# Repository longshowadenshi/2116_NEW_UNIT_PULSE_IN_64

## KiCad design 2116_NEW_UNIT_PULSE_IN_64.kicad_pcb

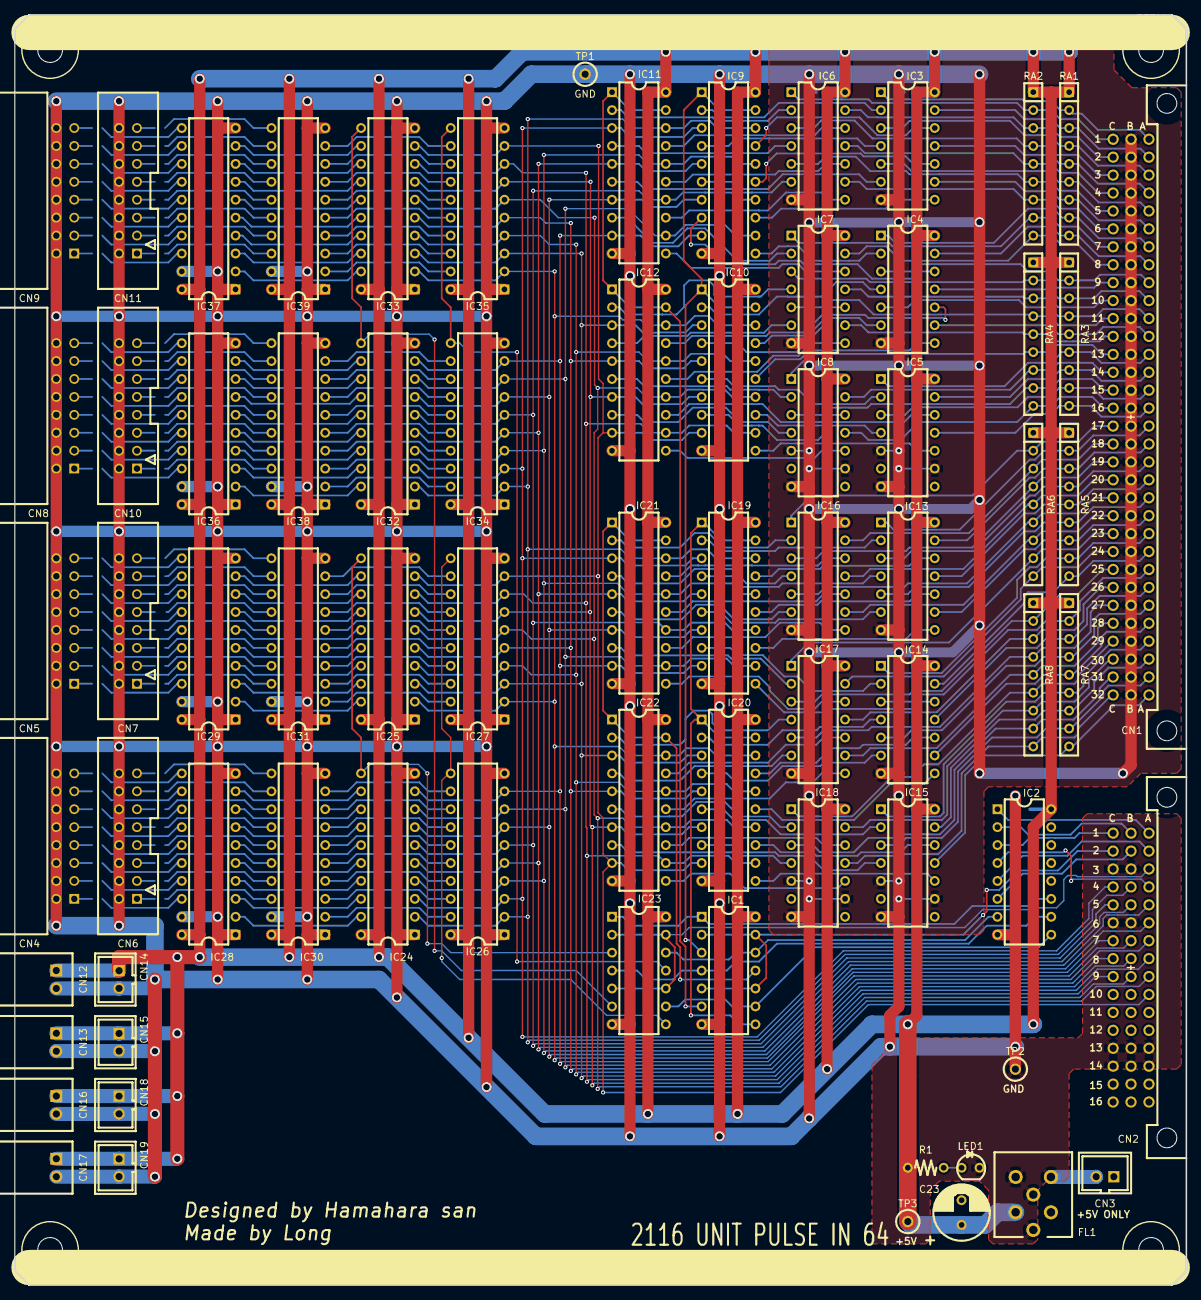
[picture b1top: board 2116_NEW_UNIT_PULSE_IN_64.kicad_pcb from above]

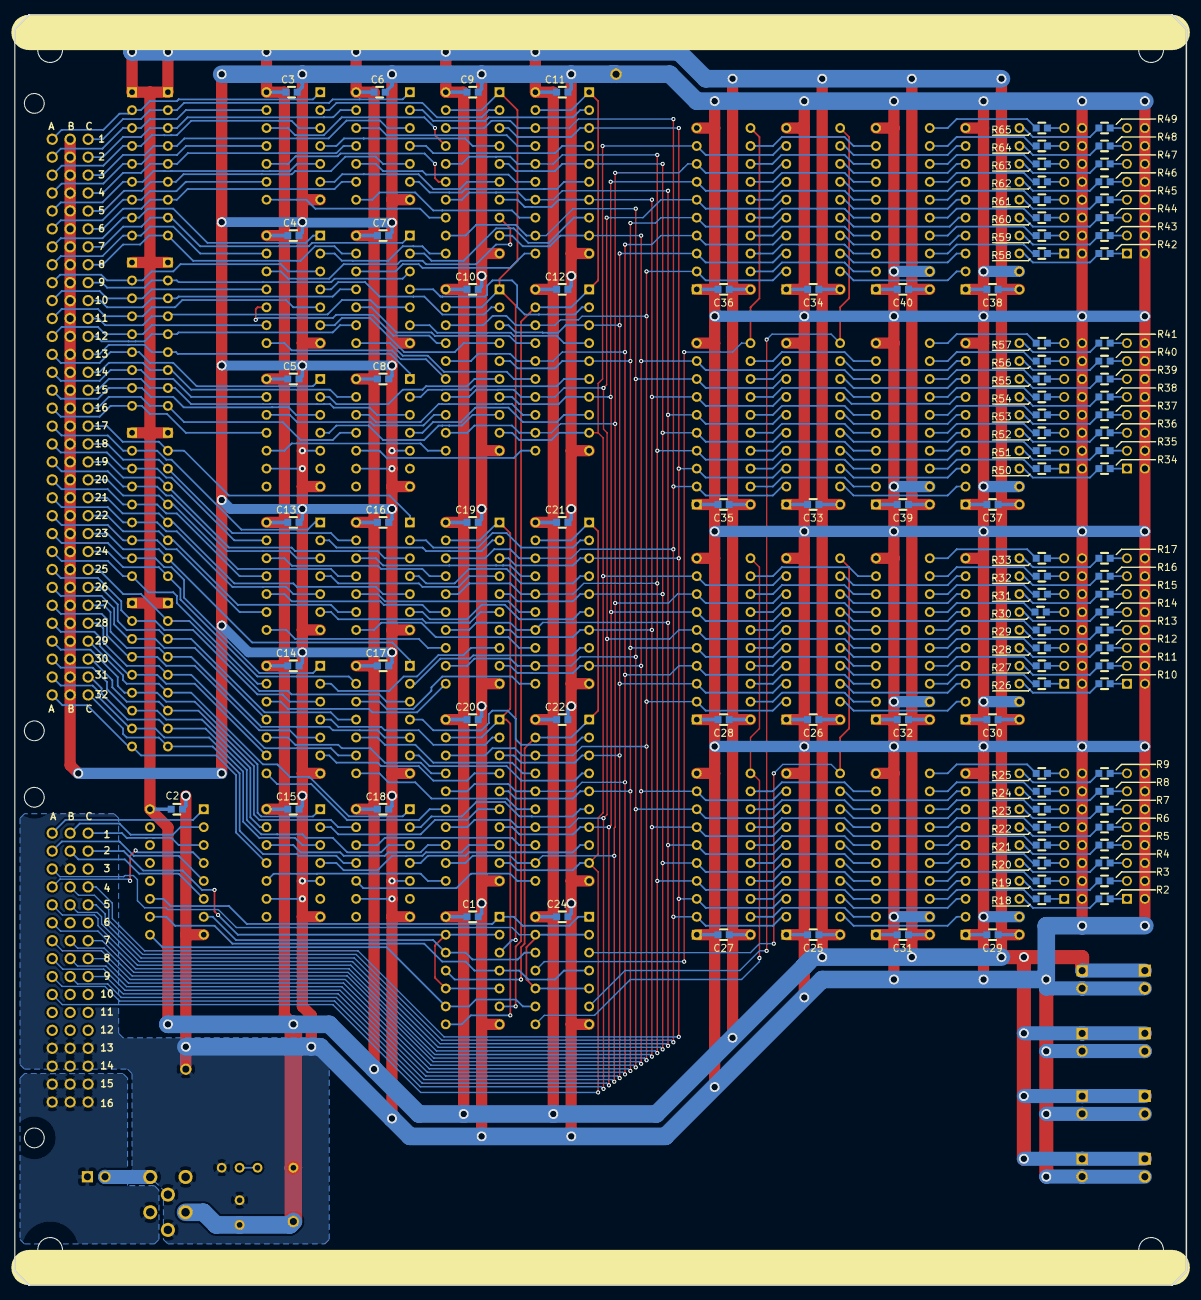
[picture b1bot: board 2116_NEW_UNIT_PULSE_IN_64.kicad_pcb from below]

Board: 2 copper layers, 166.0 x 180.0 mm, 176 parts (103 on the bottom side), 360 nets.

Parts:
C1, C2, C3, C4, C5, C6, C7, C8, C9, C10, C11, C12, C13, C14, C15, C16, C17, C18, C19, C20, C21, C22, C24, C25, C26, C27, C28, C29, C30, C31, C32, C33, C34, C35, C36, C37, C38, C39, C40: 0.1uF; C_0603
C23: 470uF/10V; CP_D8_P3R5
CN1: 09031966921; cn_09031966921
CN2: 09232486824; cn_09282486801
CN3, CN14, CN15, CN18, CN19: B2B-XH-A; cn_B2B-XH-A
CN4, CN5, CN8, CN9: HIF3FC-16PA-2.54DS; cn_HIF3FC-16PA-254DS
CN6, CN7, CN10, CN11: HIF3FC-16PA-2.54DSA; cn_HIF3FC-16PA-254DSA
CN12, CN13, CN16, CN17: S2B-XH-A
FL1: BNX002-01
IC1, IC23: 74HCT32; IC_DIP-14_W7.62mm
IC2: 74HCT138; ic_DIP-16_W7.62mm
IC3, IC4, IC5, IC6, IC7, IC8, IC13, IC14, IC15, IC16, IC17, IC18: 74HC14; IC_DIP-14_W7.62mm
IC9, IC10, IC11, IC12, IC19, IC20, IC21, IC22: 74HC244; ic_DIP-20_W7.62mm
IC24, IC25, IC26, IC27, IC32, IC33, IC34, IC35: 74HCT574; ic_DIP-20_W7.62mm
IC28, IC29, IC30, IC31, IC36, IC37, IC38, IC39: 74HCT541; ic_DIP-20_W7.62mm
LED1: GREEN; LED_D3.0mm_center
R1: 470; R_TH_5R08
R2, R3, R4, R5, R6, R7, R8, R9, R10, R11, R12, R13, R14, R15, R16, R17, R18, R19, R20, R21, R22, R23, R24, R25, R26, R27, R28, R29, R30, R31, R32, R33, R34, R35, R36, R37, R38, R39, R40, R41, R42, R43, R44, R45, R46, R47, R48, R49, R50, R51, R52, R53, R54, R55, R56, R57, R58, R59, R60, R61, R62, R63, R64, R65: 470; C_0603
RA1, RA2, RA3, RA4, RA5, RA6, RA7, RA8: 4.7K * 8; RKC1_8B8
TP1, TP2: ST-2-1; LC-2-G
TP3: LC-2-G

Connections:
+5V: C1.1, C2.1, C3.1, C4.1, C5.1, C6.1, C7.1, C8.1, C9.1, C10.1, C11.1, C12.1, C13.1, C14.1, C15.1, C16.1, C17.1, C18.1, C19.1, C20.1, C21.1, C22.1, C23.1, C24.1, C25.1, C26.1, C27.1, C28.1, C29.1, C30.1, C31.1, C32.1, C33.1, C34.1, C35.1, C36.1, C37.1, C38.1, C39.1, C40.1, CN12.1, CN13.1, CN14.1, CN15.1, CN16.1, CN17.1, CN18.1, CN19.1, FL1.2, IC1.14, IC2.16, IC3.14, IC4.14, IC5.14, IC6.14, IC7.14, IC8.14, IC9.20, IC10.20, IC11.20, IC12.20, IC13.14, IC14.14, IC15.14, IC16.14, IC17.14, IC18.14, IC19.20, IC20.20, IC21.20, IC22.20, IC23.14, IC24.20, IC25.20, IC26.20, IC27.20, IC28.20, IC29.20, IC30.20, IC31.20, IC32.20, IC33.20, IC34.20, IC35.20, IC36.20, IC37.20, IC38.20, IC39.20, R1.1, RA1.1, RA2.1, RA3.1, RA4.1, RA5.1, RA6.1, RA7.1, RA8.1, TP3.1
/A0: CN2.1A, IC2.1
/A1: CN2.1B, IC2.2
/A2: CN2.1C, IC2.3
/A3: CN2.2A, IC2.5
/A4: CN2.2B, IC2.6
/C_ENB: CN2.4A, IC2.4
/D0: CN2.4B, IC9.18, IC11.18, IC19.18, IC21.18, IC24.2, IC26.2, IC32.2, IC34.2
/D1: CN2.4C, IC9.3, IC11.3, IC19.3, IC21.3, IC24.3, IC26.3, IC32.3, IC34.3
/D2: CN2.5A, IC9.16, IC11.16, IC19.16, IC21.16, IC24.4, IC26.4, IC32.4, IC34.4
/D3: CN2.5B, IC9.5, IC11.5, IC19.5, IC21.5, IC24.5, IC26.5, IC32.5, IC34.5
/D4: CN2.5C, IC9.14, IC11.14, IC19.14, IC21.14, IC24.6, IC26.6, IC32.6, IC34.6
/D5: CN2.6A, IC9.7, IC11.7, IC19.7, IC21.7, IC24.7, IC26.7, IC32.7, IC34.7
/D6: CN2.7A, IC9.12, IC11.12, IC19.12, IC21.12, IC24.8, IC26.8, IC32.8, IC34.8
/D7: CN2.7B, IC9.9, IC11.9, IC19.9, IC21.9, IC24.9, IC26.9, IC32.9, IC34.9
/D8: CN2.7C, IC10.18, IC12.18, IC20.18, IC22.18, IC25.2, IC27.2, IC33.2, IC35.2
/D9: CN2.8A, IC10.3, IC12.3, IC20.3, IC22.3, IC25.3, IC27.3, IC33.3, IC35.3
/D10: CN2.8B, IC10.16, IC12.16, IC20.16, IC22.16, IC25.4, IC27.4, IC33.4, IC35.4
/D11: CN2.8C, IC10.5, IC12.5, IC20.5, IC22.5, IC25.5, IC27.5, IC33.5, IC35.5
/D12: CN2.9A, IC10.14, IC12.14, IC20.14, IC22.14, IC25.6, IC27.6, IC33.6, IC35.6
/D13: CN2.9B, IC10.7, IC12.7, IC20.7, IC22.7, IC25.7, IC27.7, IC33.7, IC35.7
/D14: CN2.9C, IC10.12, IC12.12, IC20.12, IC22.12, IC25.8, IC27.8, IC33.8, IC35.8
/D15: CN2.10A, IC10.9, IC12.9, IC20.9, IC22.9, IC25.9, IC27.9, IC33.9, IC35.9
/PULSE_IN_01/P01: CN1.1A, IC3.1, RA1.2
/PULSE_IN_01/P02: CN1.2A, IC3.13, RA1.3
/PULSE_IN_01/P03: CN1.3A, IC3.3, RA1.4
/PULSE_IN_01/P04: CN1.4A, IC3.11, RA1.5
/PULSE_IN_01/P05: CN1.5A, IC3.5, RA1.6
/PULSE_IN_01/P06: CN1.6A, IC3.9, RA1.7
/PULSE_IN_01/P07: CN1.7A, IC4.1, RA1.8
/PULSE_IN_01/P08: CN1.8A, IC4.13, RA1.9
/PULSE_IN_01/P09: CN1.9A, IC4.3, RA3.2
/PULSE_IN_01/P10: CN1.10A, IC4.11, RA3.3
/PULSE_IN_01/P11: CN1.11A, IC4.5, RA3.4
/PULSE_IN_01/P12: CN1.12A, IC4.9, RA3.5
/PULSE_IN_01/P13: CN1.13A, IC5.1, RA3.6
/PULSE_IN_01/P14: CN1.14A, IC5.13, RA3.7
/PULSE_IN_01/P15: CN1.15A, IC5.3, RA3.8
/PULSE_IN_01/P16: CN1.16A, IC5.11, RA3.9
/PULSE_IN_01/P17: CN1.1C, IC6.1, RA2.2
/PULSE_IN_01/P18: CN1.2C, IC6.13, RA2.3
/PULSE_IN_01/P19: CN1.3C, IC6.3, RA2.4
/PULSE_IN_01/P20: CN1.4C, IC6.11, RA2.5
/PULSE_IN_01/P21: CN1.5C, IC6.5, RA2.6
/PULSE_IN_01/P22: CN1.6C, IC6.9, RA2.7
/PULSE_IN_01/P23: CN1.7C, IC7.1, RA2.8
/PULSE_IN_01/P24: CN1.8C, IC7.13, RA2.9
/PULSE_IN_01/P25: CN1.9C, IC7.3, RA4.2
/PULSE_IN_01/P26: CN1.10C, IC7.11, RA4.3
/PULSE_IN_01/P27: CN1.11C, IC7.5, RA4.4
/PULSE_IN_01/P28: CN1.12C, IC7.9, RA4.5
/PULSE_IN_01/P29: CN1.13C, IC8.1, RA4.6
/PULSE_IN_01/P30: CN1.14C, IC8.13, RA4.7
/PULSE_IN_01/P31: CN1.15C, IC8.3, RA4.8
/PULSE_IN_01/P32: CN1.16C, IC8.11, RA4.9
/PULSE_IN_01/Q01: IC3.2, IC9.2
/PULSE_IN_01/Q02: IC3.12, IC9.17
/PULSE_IN_01/Q03: IC3.4, IC9.4
/PULSE_IN_01/Q04: IC3.10, IC9.15
/PULSE_IN_01/Q05: IC3.6, IC9.6
/PULSE_IN_01/Q06: IC3.8, IC9.13
/PULSE_IN_01/Q07: IC4.2, IC9.11
/PULSE_IN_01/Q08: IC4.12, IC9.8
/PULSE_IN_01/Q09: IC4.4, IC10.2
/PULSE_IN_01/Q10: IC4.10, IC10.17
/PULSE_IN_01/Q11: IC4.6, IC10.4
/PULSE_IN_01/Q12: IC4.8, IC10.15
/PULSE_IN_01/Q13: IC5.2, IC10.6
/PULSE_IN_01/Q14: IC5.12, IC10.13
/PULSE_IN_01/Q15: IC5.4, IC10.8
/PULSE_IN_01/Q16: IC5.10, IC10.11
/PULSE_IN_01/Q17: IC6.2, IC11.2
/PULSE_IN_01/Q18: IC6.12, IC11.17
/PULSE_IN_01/Q19: IC6.4, IC11.4
/PULSE_IN_01/Q20: IC6.10, IC11.15
/PULSE_IN_01/Q21: IC6.6, IC11.6
/PULSE_IN_01/Q22: IC6.8, IC11.13
/PULSE_IN_01/Q23: IC7.2, IC11.8
/PULSE_IN_01/Q24: IC7.12, IC11.11
/PULSE_IN_01/Q25: IC7.4, IC12.2
/PULSE_IN_01/Q26: IC7.10, IC12.17
/PULSE_IN_01/Q27: IC7.6, IC12.4
/PULSE_IN_01/Q28: IC7.8, IC12.15
/PULSE_IN_01/Q29: IC8.2, IC12.6
/PULSE_IN_01/Q30: IC8.12, IC12.13
/PULSE_IN_01/Q31: IC8.4, IC12.8
/PULSE_IN_01/Q32: IC8.10, IC12.11
/PULSE_IN_02/P33: CN1.17A, IC13.1, RA5.2
/PULSE_IN_02/P34: CN1.18A, IC13.13, RA5.3
/PULSE_IN_02/P35: CN1.19A, IC13.3, RA5.4
/PULSE_IN_02/P36: CN1.20A, IC13.11, RA5.5
/PULSE_IN_02/P37: CN1.21A, IC13.5, RA5.6
/PULSE_IN_02/P38: CN1.22A, IC13.9, RA5.7
/PULSE_IN_02/P39: CN1.23A, IC14.1, RA5.8
/PULSE_IN_02/P40: CN1.24A, IC14.13, RA5.9
/PULSE_IN_02/P41: CN1.25A, IC14.3, RA7.2
/PULSE_IN_02/P42: CN1.26A, IC14.11, RA7.3
/PULSE_IN_02/P43: CN1.27A, IC14.5, RA7.4
/PULSE_IN_02/P44: CN1.28A, IC14.9, RA7.5
/PULSE_IN_02/P45: CN1.29A, IC15.1, RA7.6
/PULSE_IN_02/P46: CN1.30A, IC15.13, RA7.7
/PULSE_IN_02/P47: CN1.31A, IC15.3, RA7.8
/PULSE_IN_02/P48: CN1.32A, IC15.11, RA7.9
/PULSE_IN_02/P49: CN1.17C, IC16.1, RA6.2
/PULSE_IN_02/P50: CN1.18C, IC16.13, RA6.3
/PULSE_IN_02/P51: CN1.19C, IC16.3, RA6.4
/PULSE_IN_02/P52: CN1.20C, IC16.11, RA6.5
/PULSE_IN_02/P53: CN1.21C, IC16.5, RA6.6
/PULSE_IN_02/P54: CN1.22C, IC16.9, RA6.7
/PULSE_IN_02/P55: CN1.23C, IC17.1, RA6.8
/PULSE_IN_02/P56: CN1.24C, IC17.13, RA6.9
/PULSE_IN_02/P57: CN1.25C, IC17.3, RA8.2
/PULSE_IN_02/P58: CN1.26C, IC17.11, RA8.3
/PULSE_IN_02/P59: CN1.27C, IC17.5, RA8.4
/PULSE_IN_02/P60: CN1.28C, IC17.9, RA8.5
/PULSE_IN_02/P61: CN1.29C, IC18.1, RA8.6
/PULSE_IN_02/P62: CN1.30C, IC18.13, RA8.7
/PULSE_IN_02/P63: CN1.31C, IC18.3, RA8.8
/PULSE_IN_02/P64: CN1.32C, IC18.11, RA8.9
/PULSE_IN_02/Q33: IC13.2, IC19.2
/PULSE_IN_02/Q34: IC13.12, IC19.17
/PULSE_IN_02/Q35: IC13.4, IC19.4
/PULSE_IN_02/Q36: IC13.10, IC19.15
/PULSE_IN_02/Q37: IC13.6, IC19.6
/PULSE_IN_02/Q38: IC13.8, IC19.13
/PULSE_IN_02/Q39: IC14.2, IC19.8
/PULSE_IN_02/Q40: IC14.12, IC19.11
/PULSE_IN_02/Q41: IC14.4, IC20.2
/PULSE_IN_02/Q42: IC14.10, IC20.17
/PULSE_IN_02/Q43: IC14.6, IC20.4
/PULSE_IN_02/Q44: IC14.8, IC20.15
/PULSE_IN_02/Q45: IC15.2, IC20.6
/PULSE_IN_02/Q46: IC15.12, IC20.13
/PULSE_IN_02/Q47: IC15.4, IC20.8
/PULSE_IN_02/Q48: IC15.10, IC20.11
/PULSE_IN_02/Q49: IC16.2, IC21.2
/PULSE_IN_02/Q50: IC16.12, IC21.17
/PULSE_IN_02/Q51: IC16.4, IC21.4
/PULSE_IN_02/Q52: IC16.10, IC21.15
/PULSE_IN_02/Q53: IC16.6, IC21.6
/PULSE_IN_02/Q54: IC16.8, IC21.13
/PULSE_IN_02/Q55: IC17.2, IC21.8
/PULSE_IN_02/Q56: IC17.12, IC21.11
/PULSE_IN_02/Q57: IC17.4, IC22.2
/PULSE_IN_02/Q58: IC17.10, IC22.17
/PULSE_IN_02/Q59: IC17.6, IC22.4
/PULSE_IN_02/Q60: IC17.8, IC22.15
/PULSE_IN_02/Q61: IC18.2, IC22.6
/PULSE_IN_02/Q62: IC18.12, IC22.13
/PULSE_IN_02/Q63: IC18.4, IC22.8
/PULSE_IN_02/Q64: IC18.10, IC22.11
/PULSE_OUT_01/OUT01: IC28.18, R2.1
/PULSE_OUT_01/OUT02: IC28.17, R3.1
/PULSE_OUT_01/OUT03: IC28.16, R4.1
/PULSE_OUT_01/OUT04: IC28.15, R5.1
/PULSE_OUT_01/OUT05: IC28.14, R6.1
/PULSE_OUT_01/OUT06: IC28.13, R7.1
/PULSE_OUT_01/OUT07: IC28.12, R8.1
/PULSE_OUT_01/OUT08: IC28.11, R9.1
/PULSE_OUT_01/OUT09: IC29.18, R10.1
/PULSE_OUT_01/OUT10: IC29.17, R11.1
/PULSE_OUT_01/OUT11: IC29.16, R12.1
/PULSE_OUT_01/OUT12: IC29.15, R13.1
/PULSE_OUT_01/OUT13: IC29.14, R14.1
/PULSE_OUT_01/OUT14: IC29.13, R15.1
/PULSE_OUT_01/OUT15: IC29.12, R16.1
/PULSE_OUT_01/OUT16: IC29.11, R17.1
/PULSE_OUT_01/OUT33: IC30.18, R18.1
/PULSE_OUT_01/OUT34: IC30.17, R19.1
/PULSE_OUT_01/OUT35: IC30.16, R20.1
/PULSE_OUT_01/OUT36: IC30.15, R21.1
/PULSE_OUT_01/OUT37: IC30.14, R22.1
/PULSE_OUT_01/OUT38: IC30.13, R23.1
/PULSE_OUT_01/OUT39: IC30.12, R24.1
/PULSE_OUT_01/OUT40: IC30.11, R25.1
/PULSE_OUT_01/OUT41: IC31.18, R26.1
/PULSE_OUT_01/OUT42: IC31.17, R27.1
/PULSE_OUT_01/OUT43: IC31.16, R28.1
/PULSE_OUT_01/OUT44: IC31.15, R29.1
/PULSE_OUT_01/OUT45: IC31.14, R30.1
/PULSE_OUT_01/OUT46: IC31.13, R31.1
/PULSE_OUT_01/OUT47: IC31.12, R32.1
/PULSE_OUT_01/OUT48: IC31.11, R33.1
/PULSE_OUT_01/Q01: IC24.19, IC28.2
/PULSE_OUT_01/Q02: IC24.18, IC28.3
/PULSE_OUT_01/Q03: IC24.17, IC28.4
/PULSE_OUT_01/Q04: IC24.16, IC28.5
/PULSE_OUT_01/Q05: IC24.15, IC28.6
/PULSE_OUT_01/Q06: IC24.14, IC28.7
/PULSE_OUT_01/Q07: IC24.13, IC28.8
/PULSE_OUT_01/Q08: IC24.12, IC28.9
/PULSE_OUT_01/Q09: IC25.19, IC29.2
/PULSE_OUT_01/Q10: IC25.18, IC29.3
/PULSE_OUT_01/Q11: IC25.17, IC29.4
/PULSE_OUT_01/Q12: IC25.16, IC29.5
/PULSE_OUT_01/Q13: IC25.15, IC29.6
/PULSE_OUT_01/Q14: IC25.14, IC29.7
/PULSE_OUT_01/Q15: IC25.13, IC29.8
/PULSE_OUT_01/Q16: IC25.12, IC29.9
/PULSE_OUT_01/Q33: IC26.19, IC30.2
/PULSE_OUT_01/Q34: IC26.18, IC30.3
/PULSE_OUT_01/Q35: IC26.17, IC30.4
/PULSE_OUT_01/Q36: IC26.16, IC30.5
/PULSE_OUT_01/Q37: IC26.15, IC30.6
/PULSE_OUT_01/Q38: IC26.14, IC30.7
/PULSE_OUT_01/Q39: IC26.13, IC30.8
/PULSE_OUT_01/Q40: IC26.12, IC30.9
/PULSE_OUT_01/Q41: IC27.19, IC31.2
/PULSE_OUT_01/Q42: IC27.18, IC31.3
/PULSE_OUT_01/Q43: IC27.17, IC31.4
/PULSE_OUT_01/Q44: IC27.16, IC31.5
/PULSE_OUT_01/Q45: IC27.15, IC31.6
/PULSE_OUT_01/Q46: IC27.14, IC31.7
/PULSE_OUT_01/Q47: IC27.13, IC31.8
/PULSE_OUT_01/Q48: IC27.12, IC31.9
/PULSE_OUT_02/OUT17: IC36.18, R34.1
/PULSE_OUT_02/OUT18: IC36.17, R35.1
/PULSE_OUT_02/OUT19: IC36.16, R36.1
/PULSE_OUT_02/OUT20: IC36.15, R37.1
/PULSE_OUT_02/OUT21: IC36.14, R38.1
/PULSE_OUT_02/OUT22: IC36.13, R39.1
/PULSE_OUT_02/OUT23: IC36.12, R40.1
/PULSE_OUT_02/OUT24: IC36.11, R41.1
/PULSE_OUT_02/OUT25: IC37.18, R42.1
/PULSE_OUT_02/OUT26: IC37.17, R43.1
/PULSE_OUT_02/OUT27: IC37.16, R44.1
/PULSE_OUT_02/OUT28: IC37.15, R45.1
/PULSE_OUT_02/OUT29: IC37.14, R46.1
/PULSE_OUT_02/OUT30: IC37.13, R47.1
/PULSE_OUT_02/OUT31: IC37.12, R48.1
/PULSE_OUT_02/OUT32: IC37.11, R49.1
/PULSE_OUT_02/OUT49: IC38.18, R50.1
/PULSE_OUT_02/OUT50: IC38.17, R51.1
/PULSE_OUT_02/OUT51: IC38.16, R52.1
/PULSE_OUT_02/OUT52: IC38.15, R53.1
/PULSE_OUT_02/OUT53: IC38.14, R54.1
/PULSE_OUT_02/OUT54: IC38.13, R55.1
/PULSE_OUT_02/OUT55: IC38.12, R56.1
/PULSE_OUT_02/OUT56: IC38.11, R57.1
/PULSE_OUT_02/OUT57: IC39.18, R58.1
/PULSE_OUT_02/OUT58: IC39.17, R59.1
/PULSE_OUT_02/OUT59: IC39.16, R60.1
/PULSE_OUT_02/OUT60: IC39.15, R61.1
/PULSE_OUT_02/OUT61: IC39.14, R62.1
/PULSE_OUT_02/OUT62: IC39.13, R63.1
/PULSE_OUT_02/OUT63: IC39.12, R64.1
/PULSE_OUT_02/OUT64: IC39.11, R65.1
/PULSE_OUT_02/Q17: IC32.19, IC36.2
/PULSE_OUT_02/Q18: IC32.18, IC36.3
/PULSE_OUT_02/Q19: IC32.17, IC36.4
/PULSE_OUT_02/Q20: IC32.16, IC36.5
/PULSE_OUT_02/Q21: IC32.15, IC36.6
/PULSE_OUT_02/Q22: IC32.14, IC36.7
/PULSE_OUT_02/Q23: IC32.13, IC36.8
/PULSE_OUT_02/Q24: IC32.12, IC36.9
/PULSE_OUT_02/Q25: IC33.19, IC37.2
/PULSE_OUT_02/Q26: IC33.18, IC37.3
/PULSE_OUT_02/Q27: IC33.17, IC37.4
/PULSE_OUT_02/Q28: IC33.16, IC37.5
/PULSE_OUT_02/Q29: IC33.15, IC37.6
/PULSE_OUT_02/Q30: IC33.14, IC37.7
/PULSE_OUT_02/Q31: IC33.13, IC37.8
/PULSE_OUT_02/Q32: IC33.12, IC37.9
/PULSE_OUT_02/Q49: IC34.19, IC38.2
/PULSE_OUT_02/Q50: IC34.18, IC38.3
/PULSE_OUT_02/Q51: IC34.17, IC38.4
/PULSE_OUT_02/Q52: IC34.16, IC38.5
/PULSE_OUT_02/Q53: IC34.15, IC38.6
/PULSE_OUT_02/Q54: IC34.14, IC38.7
/PULSE_OUT_02/Q55: IC34.13, IC38.8
/PULSE_OUT_02/Q56: IC34.12, IC38.9
/PULSE_OUT_02/Q57: IC35.19, IC39.2
/PULSE_OUT_02/Q58: IC35.18, IC39.3
/PULSE_OUT_02/Q59: IC35.17, IC39.4
/PULSE_OUT_02/Q60: IC35.16, IC39.5
/PULSE_OUT_02/Q61: IC35.15, IC39.6
/PULSE_OUT_02/Q62: IC35.14, IC39.7
/PULSE_OUT_02/Q63: IC35.13, IC39.8
/PULSE_OUT_02/Q64: IC35.12, IC39.9
/RD: CN2.2C, IC1.2, IC1.5, IC1.10, IC1.13
/SEL00: IC1.3, IC9.1, IC9.19, IC10.1, IC10.19
/SEL01: IC1.6, IC11.1, IC11.19, IC12.1, IC12.19
/SEL02: IC1.8, IC19.1, IC19.19, IC20.1, IC20.19
/SEL03: IC1.11, IC21.1, IC21.19, IC22.1, IC22.19
/W00: IC23.3, IC24.11, IC25.11
/W01: IC23.6, IC32.11, IC33.11
/W02: IC23.8, IC26.11, IC27.11
/W03: IC23.11, IC34.11, IC35.11
/WR: CN2.3A, IC23.2, IC23.5, IC23.10, IC23.13
GND: C1.2, C2.2, C3.2, C4.2, C5.2, C6.2, C7.2, C8.2, C9.2, C10.2, C11.2, C12.2, C13.2, C14.2, C15.2, C16.2, C17.2, C18.2, C19.2, C20.2, C21.2, C22.2, C23.2, C24.2, C25.2, C26.2, C27.2, C28.2, C29.2, C30.2, C31.2, C32.2, C33.2, C34.2, C35.2, C36.2, C37.2, C38.2, C39.2, C40.2, CN1.1B, CN1.2B, CN1.3B, CN1.4B, CN1.5B, CN1.6B, CN1.7B, CN1.8B, CN1.9B, CN1.10B, CN1.11B, CN1.12B, CN1.13B, CN1.14B, CN1.15B, CN1.16B, CN1.17B, CN1.18B, CN1.19B, CN1.20B, CN1.21B, CN1.22B, CN1.23B, CN1.24B, CN1.25B, CN1.26B, CN1.27B, CN1.28B, CN1.29B, CN1.30B, CN1.31B, CN1.32B, CN2.3B, CN2.3C, CN2.6B, CN2.6C, CN2.13A, CN2.13B, CN2.13C, CN2.14A, CN2.14B, CN2.14C, CN3.2, CN4.2, CN4.4, CN4.6, CN4.8, CN4.10, CN4.12, CN4.14, CN4.16, CN5.2, CN5.4, CN5.6, CN5.8, CN5.10, CN5.12, CN5.14, CN5.16, CN6.2, CN6.4, CN6.6, CN6.8, CN6.10, CN6.12, CN6.14, CN6.16, CN7.2, CN7.4, CN7.6, CN7.8, CN7.10, CN7.12, CN7.14, CN7.16, CN8.2, CN8.4, CN8.6, CN8.8, CN8.10, CN8.12, CN8.14, CN8.16, CN9.2, CN9.4, CN9.6, CN9.8, CN9.10, CN9.12, CN9.14, CN9.16, CN10.2, CN10.4, CN10.6, CN10.8, CN10.10, CN10.12, CN10.14, CN10.16, CN11.2, CN11.4, CN11.6, CN11.8, CN11.10, CN11.12, CN11.14, CN11.16, CN12.2, CN13.2, CN14.2, CN15.2, CN16.2, CN17.2, CN18.2, CN19.2, FL1.3, FL1.4, FL1.5, FL1.6, IC1.7, IC2.8, IC3.7, IC4.7, IC5.5, IC5.7, IC5.9, IC6.7, IC7.7, IC8.5, IC8.7, IC8.9, IC9.10, IC10.10, IC11.10, IC12.10, IC13.7, IC14.7, IC15.5, IC15.7, IC15.9, IC16.7, IC17.7, IC18.5, IC18.7, IC18.9, IC19.10, IC20.10, IC21.10, IC22.10, IC23.7, IC24.1, IC24.10, IC25.1, IC25.10, IC26.1, IC26.10, IC27.1, IC27.10, IC28.1, IC28.10, IC28.19, IC29.1, IC29.10, IC29.19, IC30.1, IC30.10, IC30.19, IC31.1, IC31.10, IC31.19, IC32.1, IC32.10, IC33.1, IC33.10, IC34.1, IC34.10, IC35.1, IC35.10, IC36.1, IC36.10, IC36.19, IC37.1, IC37.10, IC37.19, IC38.1, IC38.10, IC38.19, IC39.1, IC39.10, IC39.19, LED1.2, TP1.1, TP2.1
unnamed: CN4.1, R2.2
unnamed: CN4.3, R3.2
unnamed: CN4.5, R4.2
unnamed: CN4.7, R5.2
unnamed: CN4.9, R6.2
unnamed: CN4.11, R7.2
unnamed: CN4.13, R8.2
unnamed: CN4.15, R9.2
unnamed: CN5.1, R10.2
unnamed: CN5.3, R11.2
unnamed: CN5.5, R12.2
unnamed: CN5.7, R13.2
unnamed: CN5.9, R14.2
unnamed: CN5.11, R15.2
unnamed: CN5.13, R16.2
unnamed: CN5.15, R17.2
unnamed: CN6.1, R18.2
unnamed: CN6.3, R19.2
unnamed: CN6.5, R20.2
unnamed: CN6.7, R21.2
unnamed: CN6.9, R22.2
unnamed: CN6.11, R23.2
unnamed: CN6.13, R24.2
unnamed: CN6.15, R25.2
unnamed: CN7.1, R26.2
unnamed: CN7.3, R27.2
unnamed: CN7.5, R28.2
unnamed: CN7.7, R29.2
unnamed: CN7.9, R30.2
unnamed: CN7.11, R31.2
unnamed: CN7.13, R32.2
unnamed: CN7.15, R33.2
unnamed: CN8.1, R34.2
unnamed: CN8.3, R35.2
unnamed: CN8.5, R36.2
unnamed: CN8.7, R37.2
unnamed: CN8.9, R38.2
unnamed: CN8.11, R39.2
unnamed: CN8.13, R40.2
unnamed: CN8.15, R41.2
unnamed: CN9.1, R42.2
unnamed: CN9.3, R43.2
unnamed: CN9.5, R44.2
unnamed: CN9.7, R45.2
unnamed: CN9.9, R46.2
unnamed: CN9.11, R47.2
unnamed: CN9.13, R48.2
unnamed: CN9.15, R49.2
unnamed: CN10.1, R50.2
unnamed: CN10.3, R51.2
unnamed: CN10.5, R52.2
unnamed: CN10.7, R53.2
unnamed: CN10.9, R54.2
unnamed: CN10.11, R55.2
unnamed: CN10.13, R56.2
unnamed: CN10.15, R57.2
unnamed: CN11.1, R58.2
unnamed: CN11.3, R59.2
unnamed: CN11.5, R60.2
unnamed: CN11.7, R61.2
unnamed: CN11.9, R62.2
unnamed: CN11.11, R63.2
unnamed: CN11.13, R64.2
unnamed: CN11.15, R65.2
unnamed: IC1.1, IC2.11, IC23.1
unnamed: IC1.4, IC2.10, IC23.4
unnamed: IC1.9, IC2.9, IC23.9
unnamed: IC1.12, IC2.7, IC23.12
unnamed: LED1.1, R1.2
VDD: CN2.15A, CN2.15B, CN2.15C, CN2.16A, CN2.16B, CN2.16C, CN3.1, FL1.1
